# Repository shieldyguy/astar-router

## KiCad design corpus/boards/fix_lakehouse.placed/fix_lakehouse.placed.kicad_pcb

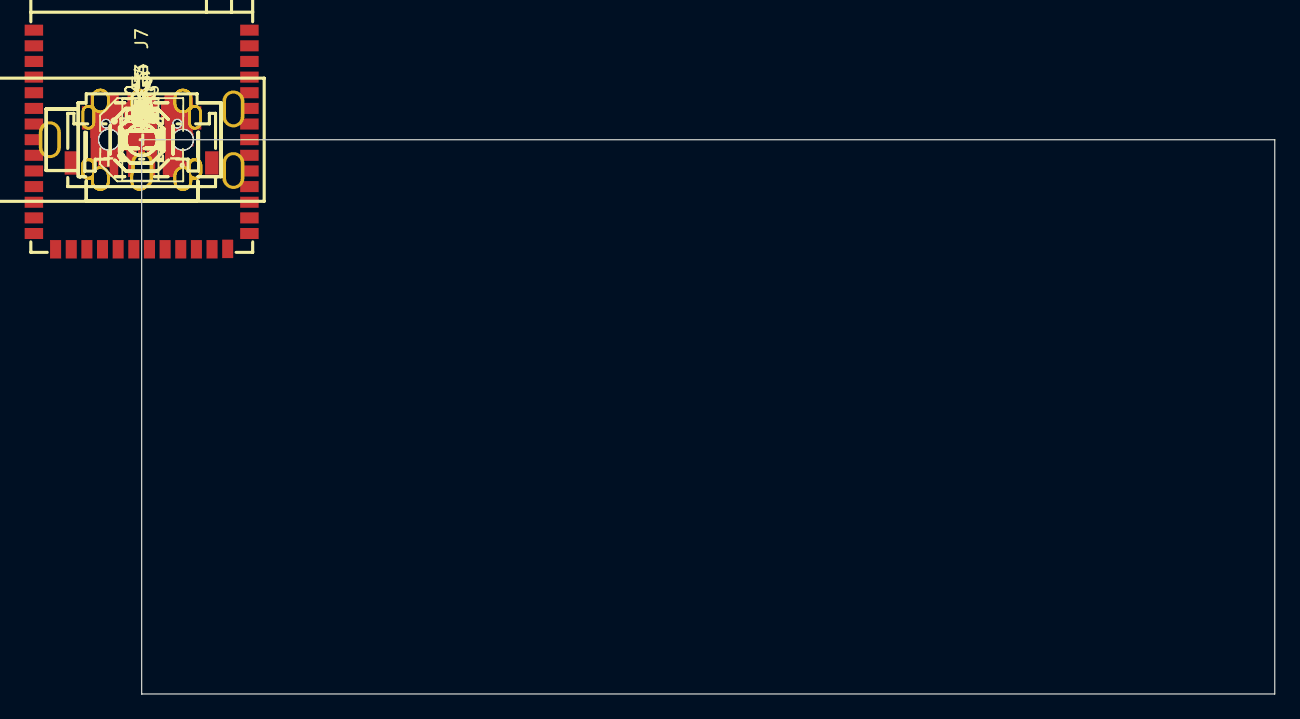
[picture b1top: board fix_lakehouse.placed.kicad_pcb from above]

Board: 2 copper layers, 92.0 x 45.0 mm, 47 parts (0 on the bottom side), 41 nets, no tracks yet.

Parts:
C1, C4, C6, C9, C10: 10uF; C0603
C2, C5, C7, C17: 100nF; C0603
C3: 220uF; CAP-SMD_BD6.3-L6.6-W6.6-FD
C8, C13, C14, C15, C16: 1uF; C0603
C11, C12: 2.2uF; C0603
D1: RUN; LED-SMD_L1.6-W0.8-R-RD
J1: POWER; USB-C-SMD_TYPE-C-16PIN-2MD-073
J2: OTG; USB-C-SMD_TYPE-C-16PIN-2MD-073
J3: OUT; AUDIO-TH_PJ-3136-B
J4: IN; AUDIO-TH_PJ-3136-B
J5: DSP_AUDIO; CONN-SMD_S6B-ZR-SM4A-TF
J6: DSP_LINK; CONN-SMD_4P-P1.50_S4B-ZR-SM4A-TF-LF-SN
J7: SUSTAIN; AUDIO-TH_PJ-603
R1, R2, R5, R6: 5.1kΩ; R0603
R3, R7, R14, R15: 10kΩ; R0603
R4, R13: 1kΩ; R0603
R8: 100kΩ; R0603
R9: 47kΩ; R0603
R10: 62kΩ; R0603
R11, R12: 100Ω; R0603
SW1: RESET; SW-SMD_4P-L5.1-W5.1-P3.70-LS6.5-TL_H1.5
SW2: BOOT; SW-SMD_4P-L5.1-W5.1-P3.70-LS6.5-TL_H1.5
U1: ESP32-S3; WIRELM-SMD_ESP32-S3-WROOM-1
U2: AMS1117-3.3; SOT-223-3_L6.5-W3.4-P2.30-LS7.0-BR
U3: USBLC6-2SC6; SOT-23-6_L2.9-W1.6-P0.95-LS2.8-BL
U4: SY6280AAAC; TSOT-23-5_L2.9-W1.6-P0.95-LS2.8-BL
U5: TPA6132A2; WQFN-16_L3.0-W3.0-P0.50-TL-EP1.6

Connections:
+3V3: C3.1, C4.1, C5.1, C6.1, C7.1, C11.1, R3.1, R14.1, U1.2, U2.2, U2.4, U5.14
+5V: C1.1, C2.1, C9.1, J1.A4B9, J1.B4A9, J6.1, U2.3, U4.5
AUX_L: C15.1, J5.2
AUX_R: C16.1, J5.3
GND: C1.2, C2.2, C3.2, C4.2, C5.2, C6.2, C7.2, C8.2, C9.2, C10.2, C11.2, C12.2, C13.2, C17.2, D1.2, J1.13, J1.14, J1.A1B12, J1.B1A12, J2.13, J2.14, J2.A1B12, J2.B1A12, J3.2, J4.2, J5.1, J5.4, J6.4, J7.2, R1.2, R2.2, R5.2, R6.2, R7.2, R8.2, R10.2, R15.2, SW1.3, SW2.3, U1.1, U1.40, U1.41, U2.1, U3.2, U4.2, U5.2, U5.3, U5.10, U5.15, U5.17
HOST_EN: R8.1, U1.6, U4.4
HP_EN: U1.7, U5.13
HP_G0: U1.8, U5.6
HP_G1: U1.9, U5.7
IN_L: J5.6, R11.2
IN_R: J5.5, R12.2
unnamed: D1.1, R4.2
unnamed: J1.A5, R1.1
unnamed: J1.B5, R2.1
unnamed: J2.A5, R5.1
unnamed: J2.B5, R6.1
unnamed: J4.3, R12.1
unnamed: J4.4, R11.1
unnamed: J7.3, R15.1
unnamed: J7.4, R13.1
unnamed: C8.1, R3.2, SW1.1, U1.3
unnamed: SW2.1, U1.27
unnamed: R9.2, R10.1, U1.5
unnamed: R4.1, U1.25
unnamed: R7.1, U4.3
unnamed: C14.2, U5.9
unnamed: C14.1, U5.11
unnamed: C12.1, U5.12
unnamed: C13.1, U5.8
unnamed: C15.2, U5.1
unnamed: C16.2, U5.4
OTG_DM_C: J2.A7, J2.B7, U3.1
OTG_DP_C: J2.A6, J2.B6, U3.3
OUT_L: J3.4, U5.16
OUT_R: J3.3, U5.5
SUS: C17.1, R13.2, R14.2, U1.4
UART_RX: J6.2, U1.11
UART_TX: J6.3, U1.10
USB_DM: U1.13, U3.6
USB_DP: U1.14, U3.4
VBUS_OTG: C10.1, J2.A4B9, J2.B4A9, R9.1, U3.5, U4.1

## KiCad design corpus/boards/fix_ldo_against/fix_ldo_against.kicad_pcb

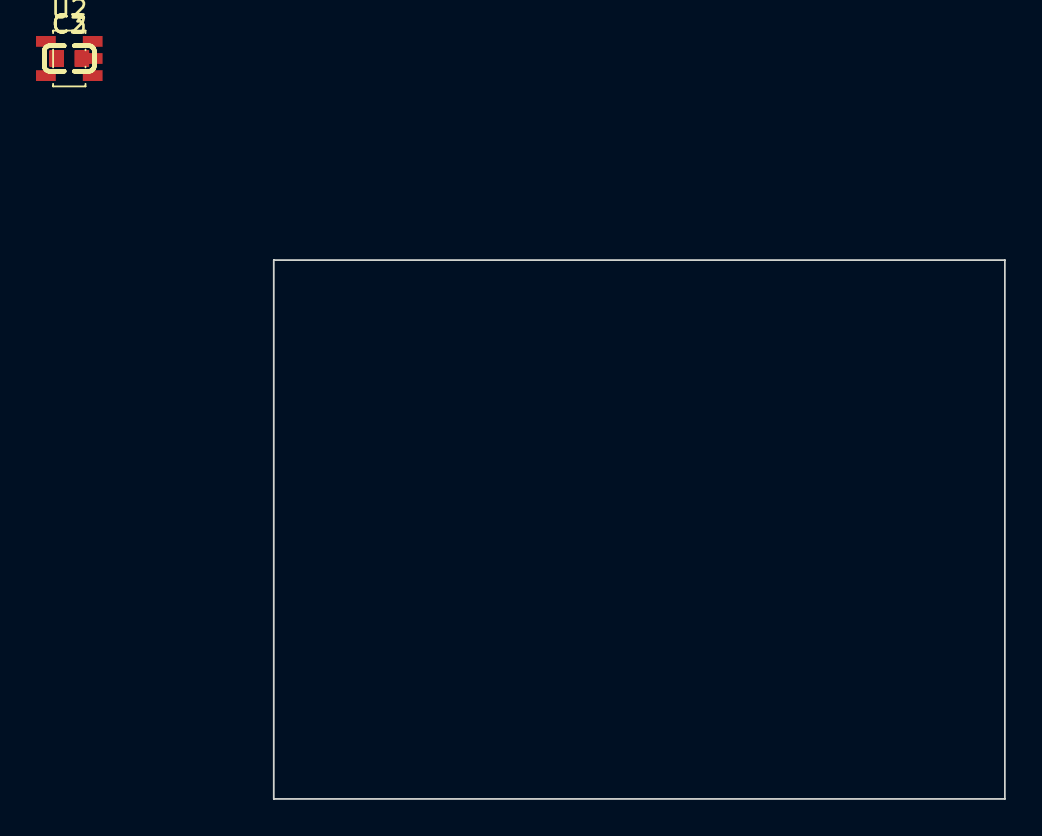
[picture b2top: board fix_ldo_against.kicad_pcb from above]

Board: 2 copper layers, 40.6 x 29.9 mm, 3 parts (0 on the bottom side), 3 nets, no tracks yet.

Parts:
C2, C3: 1uF; C0603
U2: LP5907MFX-3.3/NOPB; SOT-23-5_L3.0-W1.7-P0.95-LS2.8-BR

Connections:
GND: C2.2, C3.2, U2.2 (GND)
IN: C3.1, U2.1 (IN)
OUT: C2.1, U2.5 (OUT)

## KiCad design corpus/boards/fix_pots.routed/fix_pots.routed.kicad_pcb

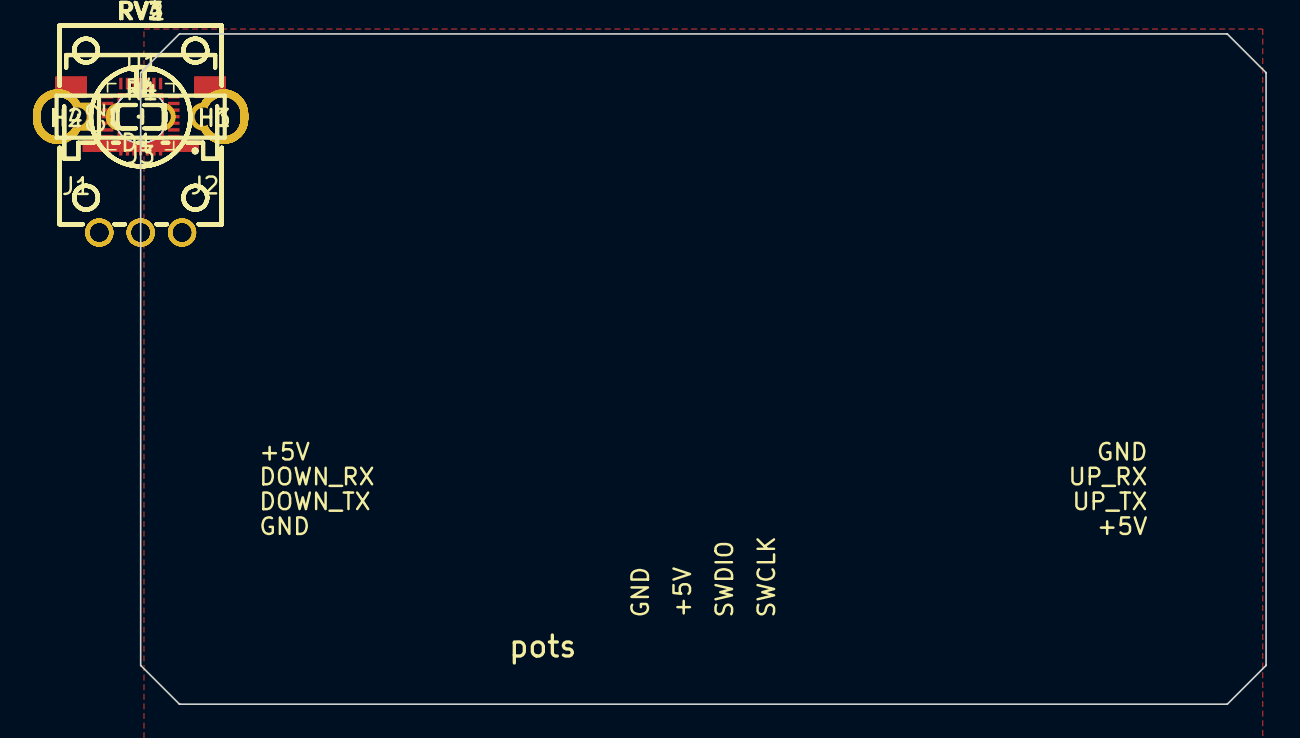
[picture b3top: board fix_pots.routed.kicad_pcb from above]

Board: 2 copper layers, 68.0 x 40.5 mm, 16 parts (0 on the bottom side), 15 nets, no tracks yet.

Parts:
C2: 10uF; C0603
D1: RUN; LED-SMD_L1.6-W0.8-R-RD
H1, H2, H3, H4: MountingHole_3.2mm_M3
J1: DOWN; CONN-SMD_4P-P1.50_S4B-ZR-SM4A-TF-LF-SN
J2: UP; CONN-SMD_4P-P1.50_S4B-ZR-SM4A-TF-LF-SN
J3: PROG; HDR-TH_4P-P2.54-V-M
R1, R4: 1kΩ; R0603
RV1, RV2, RV3, RV4: 10kΩ; RES-TH_RK09K1130A70
U1: CH32X035G8U6; QFN-28_L4.0-W4.0-P0.40-BL-EP2.8

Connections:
+5V: C2.1, J1.1, J2.1, J3.2, RV1.3, RV2.3, RV3.3, RV4.3, U1.2 (VDD)
BOOT_DN: R4.1, U1.27 (PC17/UDP/RTS1/TX4_/I2C_/RX4_/T1ET/PC10)
DOWN_RX: J1.2, U1.22 (PB11/T1C3/T2C1N_/RX1)
DOWN_TX: J1.3, U1.21 (PB10/TX1/T1C2)
GND: C2.2, D1.2, J1.4, J1.5, J1.6, J2.4, J2.5, J2.6, J3.1, R4.2, RV1.1, RV2.1, RV3.1, RV4.1, U1.29 (GND)
LED: R1.1, U1.28 (PC14/CC1/T1C3_/T2C2_)
unnamed: D1.1, R1.2
POT1: RV1.2, U1.9 (PA4/CS/O2O0/T3C2_/A4)
POT2: RV2.2, U1.10 (PA5/SCK/TX4_/O2N0/A5)
POT3: RV3.2, U1.11 (PA6/MISO/T3C1/T1BK_/O1N0/A6)
POT4: RV4.2, U1.13 (PB0/TX4/T1C2N_/O1P0/A8)
SWCLK: J3.4, U1.24 (PC19/DCK/T2C1_/T3C1_/I2C_/RX3_/C1P0)
SWDIO: J3.3, U1.25 (PC18/DIO/TX3_/T2C1N_/T3C2_/I2C_/T1ET_)
UP_RX: J2.3, U1.8 (PA3/T2C4/O1O0/T3C1_/RX2/A3)
UP_TX: J2.2, U1.7 (PA2/TX2/T2C3/O2O1/T2ET_/A2)

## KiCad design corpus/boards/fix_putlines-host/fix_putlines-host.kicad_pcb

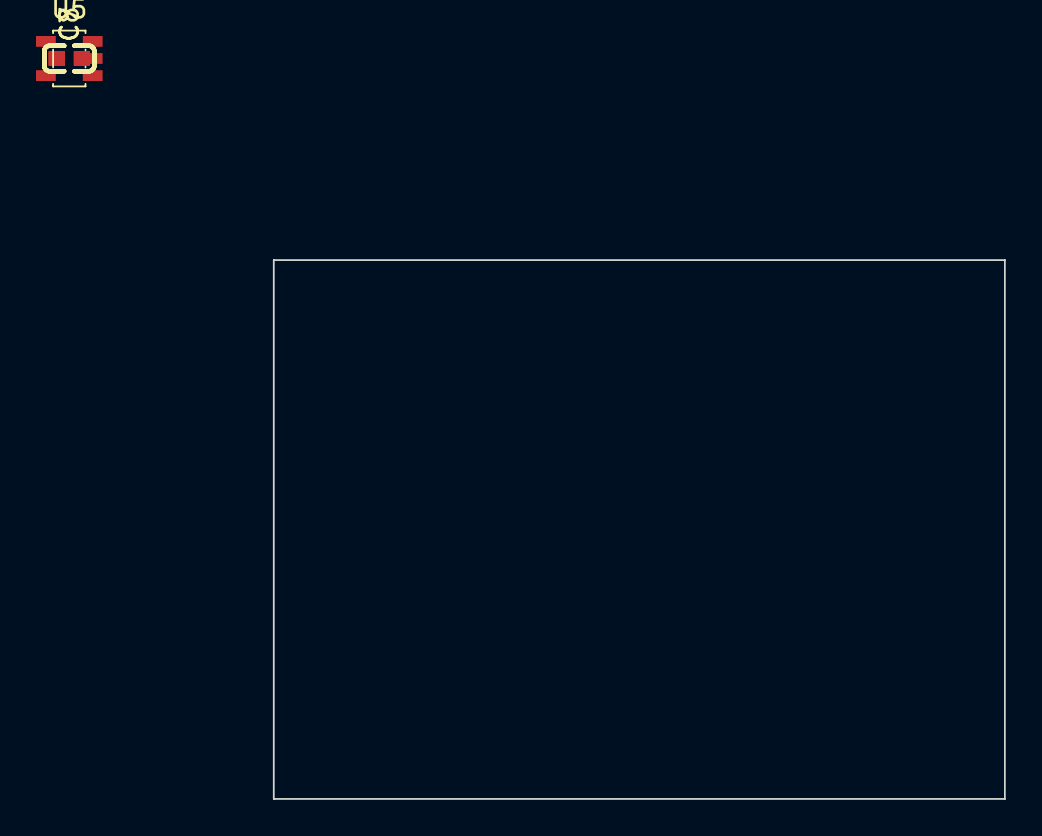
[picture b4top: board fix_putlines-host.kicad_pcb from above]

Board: 2 copper layers, 40.6 x 29.9 mm, 3 parts (0 on the bottom side), 3 nets, no tracks yet.

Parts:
C7, C8: 1uF; C0603
U5: LP5907MFX-3.3/NOPB; SOT-23-5_L3.0-W1.7-P0.95-LS2.8-BR

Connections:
GND: C7.2, C8.2, U5.2 (GND)
IN: C7.1, U5.1 (IN)
OUT: C8.1, U5.5 (OUT)

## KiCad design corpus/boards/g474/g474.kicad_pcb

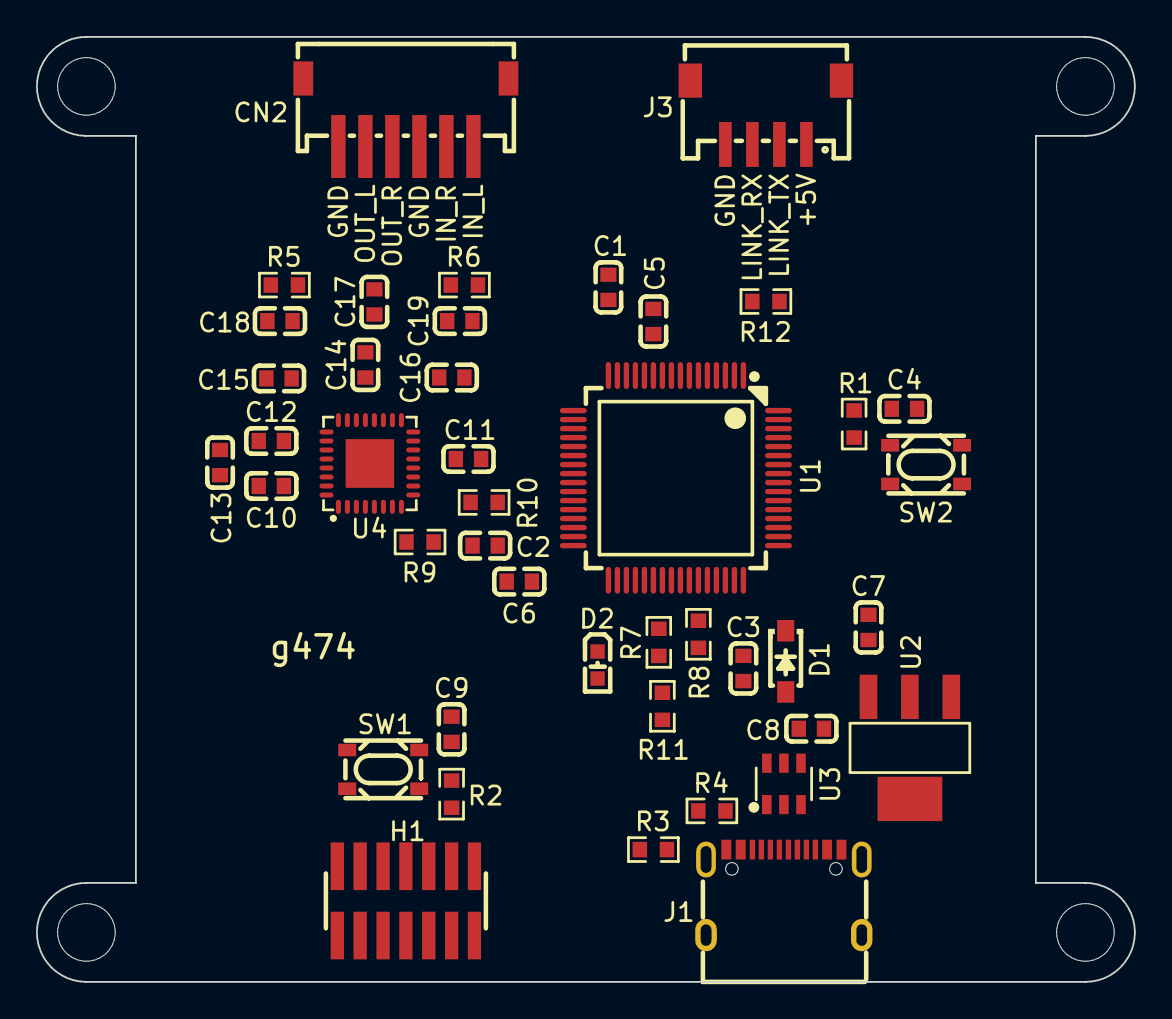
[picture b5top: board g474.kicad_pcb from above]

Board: 4 copper layers, 61.0 x 52.5 mm, 47 parts (0 on the bottom side), 41 nets, no tracks yet.

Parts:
C1, C2, C3, C4, C9: 100nF; CC0603KRX7R9BB104
C5, C7, C8, C10, C11, C12, C13, C14, C15, C16, C17: 10uF; CL10A106KP8NNNC
C6: 1uF; CL10A105KB8NNNC
C18, C19: 10nF; 0603B103K500NT
CN2: AUDIO; S6B-ZR-SM4A-TF(LF)(SN)
D1: B5819W SL; B5819W_SL
D2: RUN; KT-0603R
H1: STDC14; PZ127-2-07-S
H2, H3, H4, H5: MountingHole_3.2mm_M3
J1: USB-C; TYPE-C_16PIN_2MD(073)
J3: LINK; S4B-ZR-SM4A-TF(LF)(SN)
R1, R2, R9, R10: 10kΩ; 0603WAF1002T5E
R3, R4: 5.1kΩ; 0603WAF5101T5E
R5, R6: 100Ω; 0603WAF1000T5E
R7, R8: 4.7kΩ; 0603WAF4701T5E
R11, R12: 1kΩ; 0603WAF1001T5E
SW1: RST; GT-TC048D-H025-L1
SW2: BOOT; GT-TC048D-H025-L1
U1: STM32G473RCT6
U2: LDL1117S33R
U3: USBLC6-2SC6
U4: NAU88C22YG

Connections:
+3V3: C1.1, C2.1, C3.1, C4.1, C5.1, C6.1, C8.1, C10.1, C11.1, C12.1, H1.3, R2.2, R7.1, R8.1, SW2.4, U1.1 (VBAT), U1.16 (VDD), U1.28 (VREF+), U1.29 (VDDA), U1.32 (VDD), U1.48 (VDD), U1.64 (VDD), U2.2 (VOUT), U2.4 (VOUT), U4.13 (VDDC), U4.14 (VDDB), U4.26 (VDDSPK), U4.31 (VDDA)
+5V: C7.1, D1.1, J3.1, U2.3 (VIN)
BOOT0: R1.1, SW2.1, U1.61 (PB8-BOOT0)
DAC_L: C15.2, R5.1
DAC_R: C14.2, R6.1
GND: C1.2, C2.2, C3.2, C4.2, C5.2, C6.2, C7.2, C8.2, C9.2, C10.2, C11.2, C12.2, C13.2, C18.2, C19.2, CN2.1, CN2.4, D2.2, H1.5, H1.7, H1.11, J1.13 (EH), J1.14 (EH), J1.A1B12 (GND), J1.B1A12 (GND), J3.4, R1.2, R3.2, R4.2, R10.2, SW1.3, U1.15 (VSS), U1.27 (VSSA), U1.31 (VSS), U1.47 (VSS), U1.63 (VSS), U2.1 (GND), U3.2, U4.12 (VSSD), U4.15 (CSB/GPIO1), U4.18 (MODE), U4.24 (VSSSPK), U4.28 (VSSA), U4.33 (EP)
I2C_SCL: R7.2, U1.40 (PC8), U4.16 (SCLK)
I2C_SDA: R8.2, U1.41 (PC9), U4.17 (SDIO)
IN_L: C16.2, CN2.6
IN_R: C17.2, CN2.5
LINK_RX: R12.2, U1.55 (PD2)
LINK_TX: J3.2, U1.54 (PC12)
NRST: C9.1, H1.12, R2.1, SW1.1, U1.7 (PG10-NRST)
unnamed: D2.1, R11.2
unnamed: J1.A5 (CC1), R3.1
unnamed: J1.B5 (CC2), R4.1
unnamed: J1.A7 (Dn1), J1.B7 (Dn2), U3.1
unnamed: J1.A6 (Dp1), J1.B6 (Dp2), U3.3
unnamed: J3.3, R12.1
unnamed: R9.2, R10.1, U1.23 (PC5)
unnamed: R11.1, U1.39 (PC7)
unnamed: C14.1, U4.21 (AUXOUT1)
unnamed: C15.1, U4.22 (AUXOUT2)
unnamed: C16.1, U4.19 (LAUXIN)
unnamed: C17.1, U4.20 (RAUXIN)
unnamed: C13.1, U4.27 (VREF)
OUT_L: C18.1, CN2.2, R5.2
OUT_R: C19.1, CN2.3, R6.2
SAI_FS: U1.62 (PB9), U4.7 (FS)
SAI_MCLK: U1.17 (PA3), U4.11 (MCLK)
SAI_SCK: U1.30 (PB10), U4.8 (BCLK)
SAI_SDA: U1.9 (PC1), U4.10 (DACIN)
SAI_SDB: U1.58 (PB5), U4.9 (ADCOUT)
SWCLK: H1.6, U1.50 (PA14)
SWDIO: H1.4, U1.49 (PA13)
SWO: H1.8, U1.56 (PB3)
USB_DM: U1.45 (PA11), U3.6
USB_DP: U1.46 (PA12), U3.4
VBUS: D1.2, J1.A4B9 (VBUS), J1.B4A9 (VBUS), R9.1, U3.5
VCP_RX: H1.13, U1.53 (PC11)
VCP_TX: H1.14, U1.52 (PC10)
